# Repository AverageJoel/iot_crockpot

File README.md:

# IoT Crockpot Controller

An open-source, internet-enabled crockpot controller with a local touchscreen UI and remote Telegram control. Built on a custom single-board design around the ESP32-S3-WROOM-1-N4R2 and a 3.5" IPS capacitive touch display.

---

> **Branch: `feature/xiao-esp32c3-display-test`**
>
> The custom PCB is not yet fabricated. This branch retargets the firmware
> to a **Seeed Studio XIAO ESP32-C3** dev board wired directly to the
> 3.5" ST7796 display module. Temperature and relay are mocked in firmware
> so the full touchscreen UI can be tested without the final hardware.
>
> See [docs/wiring_xiao_display.md](docs/wiring_xiao_display.md) for the
> full wiring diagram and [docs/building.md](docs/building.md) for build
> instructions (Windows / ESP-IDF).

---

## Test hardware (this branch)

| Component | Part | Datasheet / Info |
|-----------|------|-----------------|
| MCU dev board | Seeed Studio XIAO ESP32-C3 | [Seeed Wiki](https://wiki.seeedstudio.com/XIAO_ESP32C3_Getting_Started/) |
| Display module | LCD Wiki 3.5" IPS SPI — ST7796 + FT6336U | [LCD Wiki](https://www.lcdwiki.com/3.5inch_IPS_SPI_Module_ST7796) |

## Wiring — XIAO ESP32-C3 → 3.5" ST7796 display

> The display module is **5V powered** with an onboard level converter — use the
> XIAO's `5V` pin for VCC. Signal lines (SPI + I2C) run at 3.3V and connect
> directly to the XIAO GPIOs with no additional components.

| Display pin | Signal | XIAO pin | GPIO | Notes |
|:-----------:|--------|:--------:|:----:|-------|
| 1 | VCC | **5V** | — | Must be 5V, not 3V3 |
| 2 | GND | GND | — | |
| 3 | LCD_CS | D3 | 5 | |
| 4 | LCD_RST | D1 | 3 | |
| 5 | LCD_RS (DC) | D2 | 4 | |
| 6 | SDI (MOSI) | D10 | 10 | |
| 7 | SCK | D8 | 8 | |
| 8 | LED (BL) | D0 | 2 | |
| 9 | SDO (MISO) | D9 | 9 | |
| 10 | CTP_SCL | D5 | 7 | I2C clock |
| 11 | CTP_RST | **3V3** | — | Tie high |
| 12 | CTP_SDA | D4 | 6 | I2C data |
| 13 | CTP_INT | — | — | Leave NC (polled mode) |
| 14 | SD_CS | — | — | Leave NC |

D6 / D7 (GPIO21/20) are used by the CH340 USB-UART bridge for serial monitor — do not connect these to the display.

Full ASCII diagram and pre-power checklist: [docs/wiring_xiao_display.md](docs/wiring_xiao_display.md)

## Build (this branch)

```powershell
# In PowerShell (not Git Bash — see docs/building.md)
. C:\Users\Joel\esp\esp-idf\export.ps1

cd firmware
idf.py set-target esp32c3
idf.py build
idf.py -p COM<N> flash monitor   # replace COM<N> with XIAO's CH340 port
```

---

## Main project reference — custom PCB (`main` branch)

> **Everything below this line describes the final production hardware: a custom
> ESP32-S3 PCB with AC mains power, relay, and thermocouple.**
>
> This is **not** what you need for the XIAO ESP32-C3 test setup on this branch.
> If you are here to wire up and test the display, you are done — see the
> wiring table and build commands above.

---

## Features

- **Remote Control via Telegram** — Control and monitor from anywhere; automatic safety alerts sent to Telegram on shutoff events
- **3.5" IPS Capacitive Touchscreen** — Full-color LVGL UI with OFF/WARM/LOW/HIGH controls, temperature arc, and multi-screen navigation
- **K-Type Thermocouple** — Accurate temperature monitoring via MAX31855
- **Safety System** — Auto-shutoff at 300°F, persistent sensor-error shutoff, task watchdog timer, relay fails to OFF on any fault
- **NVS Configuration** — WiFi credentials and Telegram token stored in non-volatile flash; configurable via `idf.py menuconfig`

## Architecture

Single custom PCB — ESP32-S3 handles everything directly:

```
                    ┌───────────────────────────────────────┐
                    │        ESP32-S3-WROOM-1-N4R2          │
                    │                                       │
   USB-C ──────────►│ GPIO19/20 (USB Serial/JTAG)           │
                    │                                       │
   3.5" Display ───►│ SPI2: SCK/MOSI/MISO + LCD_CS/DC/RST  │
   FT6336U Touch ──►│ I2C:  SDA/SCL + CTP_RST/INT          │
   Backlight PWM ───►│ GPIO47 (LCD_BL)                      │
                    │                                       │
   MAX31855 TC ─────►│ SPI2: MISO/SCK + TC_CS (GPIO16)      │
   Relay/SSR ───────►│ GPIO17                               │
                    │                                       │
                    │  WiFi 802.11n ──────────────► Internet│
                    └───────────────────────────────────────┘

Power: AC Mains → HLK-5M05 (5V) → AP2112K (3.3V) → ESP32 + Display + TC
```

See [docs/hardware_decisions.md](docs/hardware_decisions.md) for the full design rationale and component selection.

## Project Structure

```
iot_crockpot/
├── firmware/
│   ├── main/
│   │   ├── main.c              # Entry point, boot log, task creation
│   │   ├── crockpot.c/.h       # Core state machine (OFF/WARM/LOW/HIGH)
│   │   ├── temperature.c/.h    # MAX31855 SPI driver, thermocouple reading
│   │   ├── relay.c/.h          # GPIO relay/SSR control
│   │   ├── wifi.c/.h           # WiFi connection management
│   │   ├── telegram.c/.h       # Telegram bot (long-poll, commands, alerts)
│   │   ├── nvs_config.c/.h     # NVS read/write helpers
│   │   ├── display.c/.h        # LVGL init, lvgl_port setup
│   │   ├── display_driver.c/.h # ST7796 SPI driver (esp_lcd)
│   │   ├── touch_driver.c/.h   # FT6336U I2C driver (esp_lcd_touch)
│   │   ├── spi_bus.c/.h        # Shared SPI2 bus init
│   │   ├── gui.c/.h            # LVGL screens and widgets
│   │   ├── Kconfig.projbuild   # GPIO and WiFi/Telegram config options
│   │   └── idf_component.yml   # LVGL + esp_lcd component dependencies
│   ├── CMakeLists.txt
│   └── sdkconfig.defaults      # Default config (fonts, watchdog, etc.)
├── hardware/                   # KiCad PCB design (in progress)
│   ├── *.kicad_sch
│   ├── *.kicad_pcb
│   └── production/
├── docs/                       # Design docs and guides
│   ├── firmware_architecture.md
│   ├── firmware_plan.md
│   ├── hardware_decisions.md
│   ├── telegram_setup.md
│   ├── wiring.md
│   └── assembly.md
└── simulator/                  # Python simulator (partial)
```

## Hardware

| Component | Part | Notes |
|-----------|------|-------|
| MCU | ESP32-S3-WROOM-1-N4R2 | 4MB flash, 2MB PSRAM, LCSC C2913203 |
| Display | 3.5" IPS SPI, ST7796 controller | 480×320, 16.7M colors |
| Touch | FT6336U (on display module) | I2C, 2-point capacitive |
| Thermocouple | MAX31855 + K-type probe | SPI, ±2°C accuracy |
| Relay | Omron G5LE-1 (10A SPDT) | NO contact, fail-safe OFF |
| Power supply | HLK-5M05 | AC-DC, 5V 5W |
| 3.3V LDO | AP2112K-3.3TRG1 | 5V→3.3V for ESP32 and peripherals |
| Input protection | 0.5A slow-blow fuse + MOV | Per HLK-5M05 datasheet |

## Getting Started

### Prerequisites

- [ESP-IDF v5.2+](https://docs.espressif.com/projects/esp-idf/en/latest/esp32s3/get-started/)

### Build and Flash

```bash
cd firmware
idf.py set-target esp32s3
idf.py menuconfig        # Configure WiFi, Telegram token, GPIO pins
idf.py build
idf.py flash monitor
```

### Configuration (`idf.py menuconfig` → *IoT Crockpot*)

| Setting | Where | Default |
|---------|-------|---------|
| WiFi SSID / Password | IoT Crockpot → WiFi | (blank) |
| Telegram bot token | IoT Crockpot → Telegram | (blank) |
| Allowed Telegram chat ID | IoT Crockpot → Telegram | (blank = any) |
| All GPIO pin assignments | IoT Crockpot → SPI Bus / Display / Touch / Relay | See table below |

Credentials are saved to NVS on first boot and persist across reflashes that don't erase NVS.

### Default GPIO Assignments

| Signal | GPIO | Notes |
|--------|------|-------|
| SPI SCK | 12 | Shared: display + MAX31855 |
| SPI MOSI | 11 | |
| SPI MISO | 13 | |
| LCD CS | 10 | ST7796 |
| LCD DC | 9 | |
| LCD RST | 8 | |
| LCD BL | 47 | PWM backlight |
| Touch SDA | 5 | FT6336U I2C |
| Touch SCL | 4 | |
| Touch RST | 6 | |
| Touch INT | 7 | |
| MAX31855 CS | 16 | Thermocouple |
| Relay | 17 | SSR/relay, active-high |
| USB D- | 19 | Fixed, native USB |
| USB D+ | 20 | Fixed, native USB |

## Telegram Commands

| Command | Description |
|---------|-------------|
| `/status` | Current state, temperature, uptime, WiFi |
| `/off` | Turn off |
| `/warm` | Set to warm |
| `/low` | Set to low |
| `/high` | Set to high |
| `/help` | List commands |

Safety events (temperature limit, sensor error) automatically send an alert to the configured chat ID without requiring a command.

See [docs/telegram_setup.md](docs/telegram_setup.md) for bot creation and configuration steps.

## Safety

- Auto-shutoff above 300°F (configurable in source)
- Persistent sensor error shutoff (10 consecutive bad readings while heating)
- Relay wired normally-open — de-energizes to OFF on any fault, power loss, or firmware crash
- Task watchdog timer: control loop must tick every second or the chip resets
- Safety alerts sent via Telegram on any automatic shutoff

**WARNING:** This project involves mains voltage. Only attempt if you have relevant electrical experience. Always follow local electrical codes and safety practices.

## Development Status

### Firmware
- [x] Core state machine (OFF/WARM/LOW/HIGH, mutex-protected)
- [x] MAX31855 thermocouple SPI driver
- [x] Relay/SSR control (active-high/low configurable)
- [x] WiFi connection management (NVS credentials, retry logic)
- [x] Telegram bot (long-poll, commands, NVS token, chat ID whitelist)
- [x] Telegram safety alerts (non-blocking queue, fires on auto-shutoff)
- [x] NVS config helpers (shared wifi + telegram storage)
- [x] ST7796 SPI display driver (esp_lcd)
- [x] FT6336U I2C touch driver (esp_lcd_touch)
- [x] LVGL integration (esp_lvgl_port)
- [x] Full touchscreen UI (4 screens, arc indicator, status bar, toast overlay)
- [x] Task watchdog timer (esp_task_wdt)
- [x] Boot log (chip info, IDF version, all GPIO pins)

### Hardware (PCB)
- [x] Architecture finalized (single-board ESP32-S3, ST7796 SPI display)
- [x] AC supply section (fuse, MOV, HLK-5M05)
- [x] Relay section (G5LE-1, 2N7002 driver, flyback diode)
- [ ] ESP32-S3 MCU section (in progress)
- [ ] USB-C connector
- [ ] AP2112K-3.3 LDO
- [ ] Display header (14-pin)
- [ ] MAX31855 thermocouple
- [ ] PCB layout
- [ ] Gerber generation
- [ ] Prototype build and validation

## Documentation

| Document | Description |
|----------|-------------|
| [firmware_architecture.md](docs/firmware_architecture.md) | Firmware module breakdown, task structure, LVGL stack |
| [hardware_decisions.md](docs/hardware_decisions.md) | Component selection rationale, ESP32-S3 vs alternatives |
| [schematic_rework_plan.md](docs/schematic_rework_plan.md) | Step-by-step KiCad schematic rework guide |
| [telegram_setup.md](docs/telegram_setup.md) | Bot creation and configuration guide |
| [building.md](docs/building.md) | Windows build guide: ESP-IDF + PowerShell, flash commands, troubleshooting |
| [wiring_xiao_display.md](docs/wiring_xiao_display.md) | XIAO ESP32-C3 → ST7796 display wiring diagram and checklist |
| [wiring.md](docs/wiring.md) | Bench wiring guide (final hardware) |
| [assembly.md](docs/assembly.md) | Assembly instructions |

## License

This project is open source. License TBD.

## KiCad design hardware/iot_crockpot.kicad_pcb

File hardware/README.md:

# IoT Crockpot Power Board

Custom PCB for the IoT Crockpot controller. Single-board design — the ESP32-S3
handles WiFi, display, thermocouple, relay, and USB directly with no secondary MCU.

## Architecture

```
AC Mains ──► Fuse ──► MOV ──► HLK-5M05 ──► P-FET ──► 5V Rail
                                           (AO3401)      │
                                         Gate: 100K→GND  │
                                         G-S: 100nF cap  │
                                                         │
                              ┌──────────────────────────┘
                              │
                              ├──► AP2112K-3.3 LDO ──► 3.3V Rail
                              │                           │
                              │              ┌────────────┘
                              │              │
                              │         ESP32-S3-WROOM-1-N4R2
                              │              │
                              │              ├──► ST7796 Display (SPI)
                              │              ├──► FT6336U Touch (I2C)
                              │              ├──► MAX31855 TC (SPI)
                              │              ├──► Relay driver (GPIO → 2N7002)
                              │              └──► USB-C (GPIO19/20, native)
                              │
                              └──► Relay coil supply (5V)

AC Mains ──► Relay NO contact ──► Crockpot heating element
```

## Project Files

- `iot_crockpot.kicad_pro` — KiCad project file
- `iot_crockpot.kicad_sch` — Top-level schematic (hierarchical sheets)
- `MCU.kicad_sch` — ESP32-S3 MCU sheet
- `power_relays_tempsens.kicad_sch` — Power supply, relay, thermocouple sheet
- `iot_crockpot.kicad_pcb` — PCB layout

## Schematic Status

| Section | Status |
|---------|--------|
| AC input (fuse, MOV, HLK-5M05) | Done |
| 5V backfeed protection (P-FET AO3401) | Pending |
| AP2112K-3.3 LDO | Pending |
| ESP32-S3-WROOM-1-N4R2 | In progress |
| USB-C connector (GCT USB4085 / HRO TYPE-C-31-M-12) | Pending |
| 14-pin display header (ST7796 + FT6336U) | Pending |
| MAX31855 thermocouple | Pending |
| Relay driver (2N7002 MOSFET) | Done |
| Relay (G5LE-1) | Done |
| Connectors (AC screw terminals, thermocouple) | Done |

See [docs/schematic_rework_plan.md](../docs/schematic_rework_plan.md) for the
step-by-step schematic rework guide.

## Components

### MCU
| Part | Value | Package | LCSC # |
|------|-------|---------|--------|
| ESP32-S3-WROOM-1-N4R2 | 4MB flash, 2MB PSRAM | Module | C2913203 |

### Display Interface
| Part | Value | Notes |
|------|-------|-------|
| J_DISPLAY | 14-pin 2.54mm header | ST7796 SPI display + FT6336U touch |

Display modules (all electrically equivalent, 14-pin 2.54mm interface):
- Hosyond (Amazon B0CMD7Y55M) ~$15
- Waveshare 3.5" Capacitive Touch LCD ~$19
- Elecrow 3.5" IPS SPI LCD ~$17

**Note:** Use ST7796 controller only. Avoid ILI9488 — no 16-bit SPI color and
broken MISO tristate cause SPI bus conflicts.

### 3.3V LDO
| Part | Value | Package | LCSC # |
|------|-------|---------|--------|
| AP2112K-3.3TRG1 | 3.3V 600mA | SOT-23-5 | (search) |

### Power Supply
| Part | Value | Notes |
|------|-------|-------|
| HLK-5M05 | 5V 5W | AC-DC isolated PSU module |

### USB
| Part | Value | LCSC # | Notes |
|------|-------|--------|-------|
| USB-C receptacle | GCT USB4085 or HRO TYPE-C-31-M-12 | C2765186 / C165948 | USB 2.0 only |
| R_D- | 22Ω 0402 | — | GPIO19 to D- |
| R_D+ | 22Ω 0402 | — | GPIO20 to D+ |
| R_CC1 | 5.1K 0402 | — | CC1 to GND |
| R_CC2 | 5.1K 0402 | — | CC2 to GND |

### AC Input Protection
| Part | Value | LCSC # | Notes |
|------|-------|--------|-------|
| Fuse holder | 5x20mm clips | C3130 | Xucheng pair |
| Fuse | 0.5A 250V slow-blow | C142839 | Littelfuse 0215.500MXP |
| MOV | 10D561K | (search) | Per HLK datasheet |

### Temperature Sensing
| Part | Value | Notes |
|------|-------|-------|
| MAX31855KASA | K-type interface | SPI, cold junction compensated |
| Thermocouple | K-type probe | High temp |

### Relay
| Part | Value | Notes |
|------|-------|-------|
| Omron G5LE-1 | SPDT 10A | 5V coil |
| 2N7002 | N-ch MOSFET | Relay driver (x2) |
| 1N4148WQ-13-F | Flyback diode | SOD-123 |
| 10K resistor | Gate pull-down | Keeps relay off when GPIO floating |

### Protection
| Part | Value | Notes |
|------|-------|-------|
| P-FET (AO3401) | SOT-23 | Blocks USB-C VBUS backfeed into HLK-5M05 |
| 100K resistor | Gate to GND | P-FET gate bias |
| 100nF cap | Gate-source | Miller coupling suppression |

### Connectors
| Part | Value | LCSC # | Notes |
|------|-------|--------|-------|
| Screw terminal (x2) | Phoenix 1935161 | (search) | AC mains in, relay out |

## GPIO Assignments

| Signal | GPIO | Notes |
|--------|------|-------|
| SPI SCK | 12 | Shared: display, MAX31855 |
| SPI MOSI | 11 | |
| SPI MISO | 13 | |
| LCD CS | 10 | |
| LCD DC | 9 | |
| LCD RST | 8 | |
| LCD BL | 47 | PWM backlight |
| SD CS | 14 | SD card on display module |
| Touch SDA | 5 | I2C |
| Touch SCL | 4 | I2C |
| Touch RST | 6 | |
| Touch INT | 7 | |
| MAX31855 CS | 16 | |
| Relay | 17 | Via 2N7002 driver |
| USB D- | 19 | Fixed, native USB |
| USB D+ | 20 | Fixed, native USB |

## ESP32-S3 Strapping Pins

| Pin | Default | Action |
|-----|---------|--------|
| GPIO0 | Pull-up to 3V3 | Ensures SPI Boot (normal) on power-up |
| GPIO46 | Float (internal pull-down) | Leave unconnected |
| EN | 10K to 3V3 + 1µF to GND | RC filter for clean power-on reset |

BOOT jumper: 2-pin 2.54mm header (GPIO0 to GND). Install to enter download mode on
next reset. Remove for normal boot. Not needed for routine flashing — native USB
handles auto-reset via esptool.py.

## Safety Notes

- **Mains Isolation**: HLK-5M05 provides isolation; maintain clearance on PCB
- **Creepage/Clearance**: Follow IPC-2221 for mains voltage traces
- **Fuse**: Must be rated for AC mains (250VAC)
- **Relay Wiring**: Use NO contact for fail-safe (de-energized = OFF)

## Fabrication Notes

1. Generate Gerbers to `production/gerbers/`
2. 2-layer board, 1.6mm thickness
3. HASL or ENIG finish
4. Minimum 2oz copper for mains traces

## References

- [Hardware Decisions](../docs/hardware_decisions.md) — Component selection rationale
- [Schematic Rework Plan](../docs/schematic_rework_plan.md) — Step-by-step rework guide
- [ESP32-S3 Hardware Design Guidelines](https://docs.espressif.com/projects/esp-hardware-design-guidelines/en/latest/esp32s3/schematic-checklist.html)
- [ST7796 Display Module](https://www.lcdwiki.com/3.5inch_IPS_SPI_Module_ST7796)
- [Omron G5LE-1 Datasheet](http://www.omron.com/ecb/products/pdf/en-g5le.pdf)

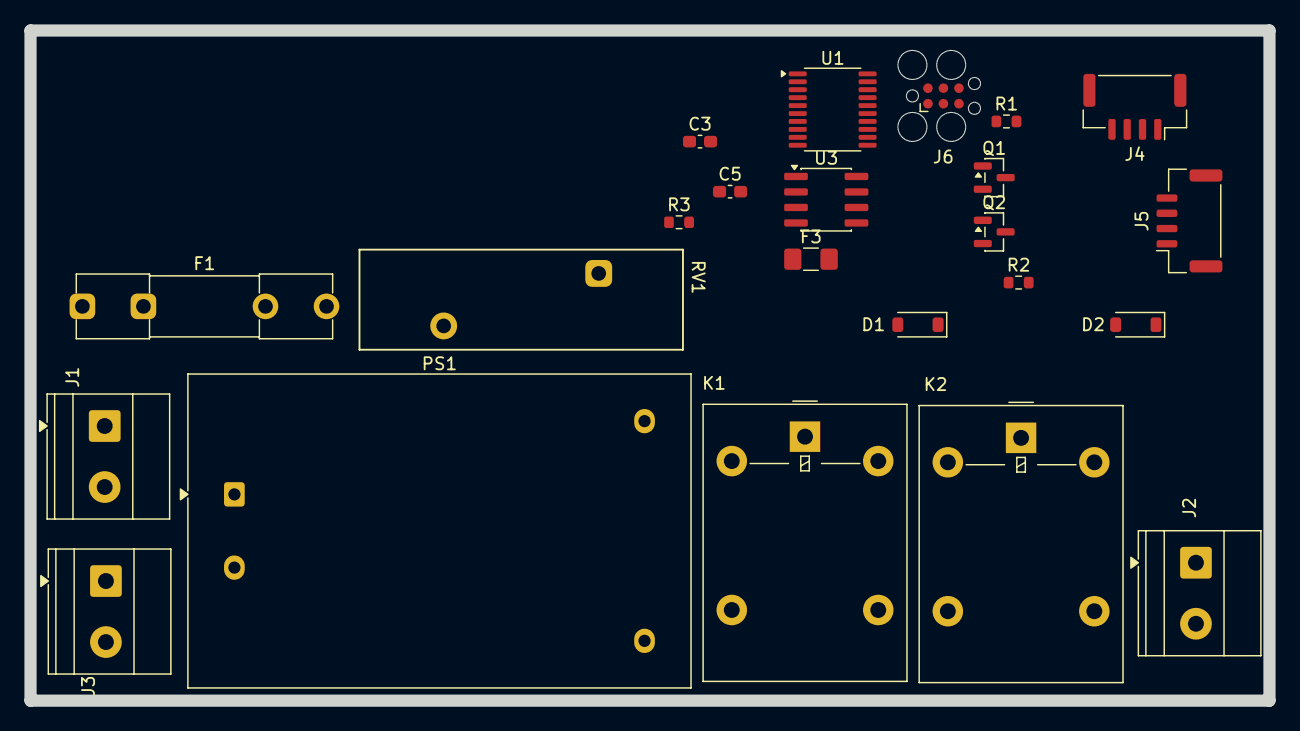
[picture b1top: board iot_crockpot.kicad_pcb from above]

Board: 2 copper layers, 101.5 x 54.9 mm, 23 parts (0 on the bottom side), 19 nets, no tracks yet.

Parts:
C3, C5: 0.1uF; C_0603_1608Metric_Pad1.08x0.95mm_HandSolder
D1, D2: 1N4148W; D_SOD-123
F1: Fuse; Fuseholder_Clip-5x20mm_Littelfuse_111_Inline_P20.00x5.00mm_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
F3: 1.5A; Fuse_1206_3216Metric_Pad1.42x1.75mm_HandSolder
J1, J2, J3: Screw_Terminal_01x02; TerminalBlock_Phoenix_MKDS-1,5-2_1x02_P5.00mm_Horizontal
J4, J5: Conn_01x04_Pin; JST_GH_SM04B-GHS-TB_1x04-1MP_P1.25mm_Horizontal
J6: Conn_ARM_SWD_TagConnect_TC2030; Tag-Connect_TC2030-IDC-FP_2x03_P1.27mm_Vertical
K1, K2: G5LE-14 5VDC; Relay_SPDT_Omron-G5LE-1
PS1: HLK-5M05; Converter_ACDC_Hi-Link_HLK-5Mxx
Q1, Q2: 2N7002; SOT-23
R1, R2, R3: 10k; R_0603_1608Metric
RV1: Varistor; RV_Rect_V25S440P_L26.5mm_W8.2mm_P12.7mm
U1: STM32G031F6Px; TSSOP-20_4.4x6.5mm_P0.65mm
U3: MAX31855KASA; SOIC-8_3.9x4.9mm_P1.27mm

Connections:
+3V3: C3.1, C5.1, J6.1 (VCC), R3.1, U1.4 (VDD), U3.4 (V_{CC})
+5V: D1.1 (K), D2.1 (K), F3.2, K1.5, K2.5
/HOT: F1.1, J1.2
/MAX31855_CS_N: R3.2, U1.12 (PA5), U3.6 (~CS)
/NEUTRAL: J1.1, RV1.2
/RELAY_1: Q2.1 (G), R2.1, U1.14 (PA7)
/RELAY_2: Q1.1 (G), R1.1, U1.15 (PA8/PB0/PB1/PB2)
/RELAY_HOT: K1.1, K2.1
/SPI1_MISO: U1.13 (PA6), U3.7 (SO)
/SPI1_SCK: U1.8 (PA1), U3.5 (SCK)
GND: C3.2, C5.2, J6.5 (GND), PS1.3 (-Vout), Q1.2 (S), Q2.2 (S), R1.2, R2.2, U1.5 (VSS), U3.1 (GND)
unnamed: F1.2, RV1.1
unnamed: D1.2 (A), K1.2, Q2.3 (D)
unnamed: D2.2 (A), K2.2, Q1.3 (D)
unnamed: J2.1, K1.4
unnamed: J2.2, K2.4
unnamed: J3.1, U3.2 (T-)
unnamed: J3.2, U3.3 (T+)
unnamed: F3.1, PS1.4 (+Vout)

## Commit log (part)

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2026-01-28 Started schematic part selection
    added XIAO ESP32-C3
    added HLK-PM01 120VAC to 5VDC power module
    added relays
    added thermal couple sensor
2026-01-28 added initial component import to pcb
    added initial component import to pcb
2026-01-30 Add cyclable menu screens with schedule builder and history
    New screens:
    - MAIN: Simplified temp display + compact state buttons (O W L H)
    - SCHEDULE_SELECT: Pick from available schedules
    - SCHEDULE_BUILDER: Create custom schedules step by step
    - HISTORY: Temperature sparkline + state timeline graph
    - SETTINGS: WiFi and display configuration
2026-01-30 Add screen select menu (press 'm')
2026-01-30 Add Menu button to bottom right of every screen
2026-01-30 Make schedule items smaller so Menu button fits
2026-01-30 Fix schedule button height and increase container size
2026-01-30 Use -> instead of > in schedule names
2026-01-30 Fix builder screen layout - smaller time buttons
2026-02-03 Schematic Updates - Power Supply
    Added architecture for power supply to schematic.
    Need to rethink control architecture. There is only two I/O exposed on
    CYD. May use second MCU on control board flashed and controlled over
    I2C by CYD.
2026-02-04 Added MCU to schematic
    Added MCU to schematic and organized circuits into blocks
2026-02-05 More Passive Part Selection
    Added passive parts/numbers and models to schematic.
    Started rough outline of PCB. Considerations will need to be done for
    angle of display in relation to height of components.
2026-02-11 Update docs for UART architecture and protection circuits
    Migrated all documentation from I2C (2-cable) to UART (1-cable)
    design. Added AP2112K-3.3 LDO, P-FET backfeed protection, and
    UART series resistor documentation. Updated BOM, pin assignments,
    architecture diagrams, and protocol tables across all docs.
2026-02-15 Document single-board ESP32-S3 architecture decision
    Finalized architecture: ESP32-S3-WROOM-1-N4R2 single-board design
    replacing CYD + STM32 two-board approach. Added ESP32 module
    comparison, USB/JTAG debugging notes, display sourcing options,
    and ST7796 vs ILI9488 analysis.
2026-02-21 Implement LVGL GUI and complete ESP32-S3 firmware stack
    Phases 1-6 of the single-board firmware plan:
    - Kconfig.projbuild: all GPIO assignments configurable via menuconfig
    - nvs_config: NVS read/write helpers; wifi + telegram load credentials at boot
    - spi_bus: shared SPI2 bus init (display + MAX31855)
    - display_driver: ST7796 SPI panel via esp_lcd (init, backlight, fill)
    - touch_driver: FT6336U I2C touch via esp_lcd_touch_ft5x06
2026-02-21 Update docs to reflect completed single-board ESP32-S3 firmware
    - README: complete rewrite for single-board design — architecture
    diagram, correct hardware table, updated build commands (esp32s3),
    GPIO table, development status, and links to new docs
    - firmware_architecture.md: new — documents module layout, FreeRTOS
    task table, full display stack, GUI screen descriptions, control
    loop with safety system, Telegram alert queue, NVS config, TWDT,
2026-02-22 Fix LVGL simulator build for Windows MSYS2 UCRT64
    - Exclude ARM Helium and NEON .S assembly (GLOB_RECURSE picked them up
    unconditionally; use TARGET_DIRECTORY set_source_files_properties)
    - Disable LVGL examples/demos build (they use disabled widgets like
    LV_USE_SLIDER and aren't needed for the simulator)
    - Add stubs for esp_lcd_panel_ops.h, esp_lcd_panel_io.h, esp_event.h
    (firmware headers transitively include these ESP-IDF headers)
2026-02-22 Add LVGL simulator feature parity: schedules, history, web API, data logging
    Firmware (shared with simulator):
    - crockpot.h: extend crockpot_status_t with relay_main/aux + schedule fields;
    add crockpot_schedule_t/step_t types, schedule API (start/stop/is_active),
    crockpot_tick_s(), crockpot_set_temp_source() hook, 3 preset schedule externs
    - crockpot.c: implement schedule engine, tick_s, temp hook, preset definitions;
    relay_main/aux populated in crockpot_get_status(); schedule cancelled on safety shutoff
2026-02-22 Expand simulator README: launch instructions, Windows internals, Telegram setup
    - Add Windows launch instructions and explain why MSYS2 shell is required
    - Add "How It Works on Windows" section with component table and runtime
    data flow diagram
    - Expand Telegram section with step-by-step enablement (OpenSSL, CMakeLists
    changes, token setup)
2026-02-22 Enable OpenSSL/TLS for Telegram; skip cert verification in simulator
    - CMakeLists.txt: switch MG_TLS from MG_TLS_NONE to MG_TLS_OPENSSL,
    link ssl and crypto (requires pacman -S mingw-w64-ucrt-x86_64-openssl)
    - telegram.c: add mg_tls_init with ca="*" in MG_EV_CONNECT to skip
    certificate verification (no system CA bundle in MSYS2 environment)
    - README: document Telegram setup steps, OpenSSL prerequisite, token
    security note, and current known issue (responses not yet working)
2026-02-26 Retarget firmware to XIAO ESP32-C3 for display/UI testing
    - Kconfig: update GPIO defaults to XIAO pinout (D0–D10); add -1 defaults
    for TC_CS, RELAY_GPIO, TOUCH_RST, TOUCH_INT (not fitted on test rig);
    add Test/Development menu with MOCK_TEMPERATURE, MOCK_RELAY, and
    LCD_DRAW_BUFFER_LINES options
    - sdkconfig.defaults: switch target to esp32c3, remove PSRAM settings,
    use UART console (CH340C on GPIO20/21), enable both mocks, set draw
2026-02-26 gitignore: exclude managed_components and simulator build output
    managed_components/ is auto-fetched by the IDF component manager from
    idf_component.yml — committing it would add 183MB (LVGL alone is 182MB).
    simulator/lvgl_sim/build/ contains compiled binaries and object files.
2026-02-26 docs: add Windows build guide for ESP-IDF firmware
    Covers how to activate the ESP-IDF environment in PowerShell,
    why Git Bash/MSYS2 does not work (MSYSTEM env var conflict),
    build and flash commands, branch/target table, XIAO ESP32-C3
    wiring, and troubleshooting for common errors hit during bring-up.
2026-02-26 docs: add XIAO ESP32-C3 display wiring diagram
    - wiring_xiao_display.md: full ASCII wiring diagram cross-referenced
    against the LCD Wiki ST7796 datasheet (14-pin header) and XIAO ESP32-C3
    pinout; includes voltage notes, per-pin table, boot sequence, and
    pre-power-on checklist
    - building.md: fix VCC wiring (3V3 → 5V); module has onboard level
    converter but needs 5V input; update pin table to use datasheet signal
2026-02-26 docs: clearly separate branch test content from main project reference
    README: add divider section between the XIAO ESP32-C3 wiring/build
    content and the main project content (ESP32-S3 custom PCB), with an
    explicit callout that everything below it is for the final hardware
    on main branch and not relevant to the display test setup.
    wiring_xiao_display.md: add scope note at the top stating this doc
    applies to the test branch only and pointing to main branch docs
2026-02-26 Fix boot crash: move button GPIOs to Kconfig, guard ISR with #if
    Hardcoded BUTTON_DOWN_GPIO=14 and BUTTON_SELECT_GPIO=15 in display.h
    were triggering ISR setup on ESP32-C3 flash-SPI pins (GPIO12-17),
    corrupting flash access and causing a TG1WDT watchdog reset loop.
    - Add Physical Buttons menu to Kconfig with UP/DOWN/SELECT GPIOs
    defaulting to -1 (not fitted); replace hardcoded defines in display.h
    - Guard button_isr_handler and init_buttons() body with #if so they
2026-02-26 fix touch: correct x_max/y_max to portrait space and verified mirror flags
    The FT6336U reports raw coordinates in portrait orientation (x=0..319,
    y=0..479). x_max/y_max are only used for mirror arithmetic (x = x_max - x),
    so they must match the pre-swap portrait dimensions — not the landscape
    LCD_H_RES/LCD_V_RES values that were previously set. Using landscape values
    shifted the mirror centre off-screen, producing a dead zone regardless of
    which mirror flags were set.
2026-02-27 feat: screensaver with LEDC PWM backlight dimming
    Replace GPIO on/off backlight with LEDC PWM (LEDC_TIMER_0, ch0, 1kHz,
    8-bit). After 60s idle the screen dims to 15% and loads a minimal
    screensaver showing current temp + heat state. Any touch restores 100%
    brightness and returns to the previous screen.
    - display_driver: LEDC init replaces gpio_config BL init; add
    display_driver_set_brightness(pct); set_backlight() delegates to it
2026-02-27 fix screensaver: ignore phantom FT6336U touch events after dim transition
    Add 1500ms lockout in touch_wake_cb after entering screensaver.
    The FT6336U in polled mode occasionally reports spurious touch data
    immediately after the screensaver screen load, causing instant wake.
    The lockout discards these events while still waking on real touches
    after the window expires.
2026-02-27 fix screensaver: raise LEDC backlight PWM from 1kHz to 25kHz
    1kHz PWM on the backlight pin (GPIO2) couples capacitively into the
    touch panel and registers as phantom FT6336U touch events, causing the
    screensaver to wake itself. 25kHz is above the touch controller noise-
    rejection threshold and eliminates the interference.
2026-02-27 fix screensaver wake: revert to indev event now that 25kHz PWM is in place
    The timer-polling approach failed because the LVGL indev driver consumes
    touch data (clears tp->data.points) on every read, so the 500ms timer
    always saw 0 touch points even during a real tap.
    The original touch_wake_cb approach works correctly now that the backlight
    PWM is at 25kHz — the phantom FT6336U touches were caused by 1kHz PWM
    coupling into the touch panel, not by any defect in the event path.
2026-02-27 feat: redesign main screen — remove arc, add 40pt temp and preset row
    Replace the decorative arc + bottom status bar layout with a cleaner
    full-screen design:
    - 28px top strip: WiFi icon, uptime, settings/info buttons
    - 112px temp panel: 40pt temperature + 20pt heat state label
    - 72px heat buttons (OFF/WARM/LOW/HIGH), now taller
    - 72px preset row: Slow Cook / Quick Warm / All Day / Custom buttons
2026-02-27 fix: improve touch responsiveness and screen transition artifacts
    Touch:
    - touch_driver.c: write FT6336U register 0x86=0x00 (keep-active mode)
    The chip defaults to auto-monitor (low-power scan between touches),
    which delays or drops the first tap after any idle period. Keep-active
    keeps it scanning at full rate continuously.
    - display.c: reduce LVGL indev poll period from ~30ms to 16ms after
2026-03-01 fix: improve display rendering and touch responsiveness
    - Increase LVGL draw buffer from 20 to 40 lines (halves flush count per frame)
    - Reduce LVGL indev poll period from 16ms to 8ms for quicker tap detection
    - Fix FT6336U PERIODACTIVE register address (0x88, not 0x80 which is THGROUP)
    — wrong address was setting touch threshold to 1, flooding LVGL with phantom
    touches and freezing the UI on any button press
    - Reduce screen transition animation from 150ms to 100ms
2026-03-02 feat: background touch task, custom indev, fade transitions
    Touch:
    - Add touch_poll_task — dedicated FreeRTOS task reads FT6336U every 8ms
    into s_cache regardless of LVGL rendering load. Previously, I2C reads
    happened inside the LVGL task which was blocked ~32ms per frame waiting
    for SPI DMA; short taps during renders were silently dropped.
    - Add touch_driver_read_cached() for instant cache reads (no I2C in LVGL)
2026-03-02 fix: enable touch INT on GPIO20 (D7) — wire is connected
